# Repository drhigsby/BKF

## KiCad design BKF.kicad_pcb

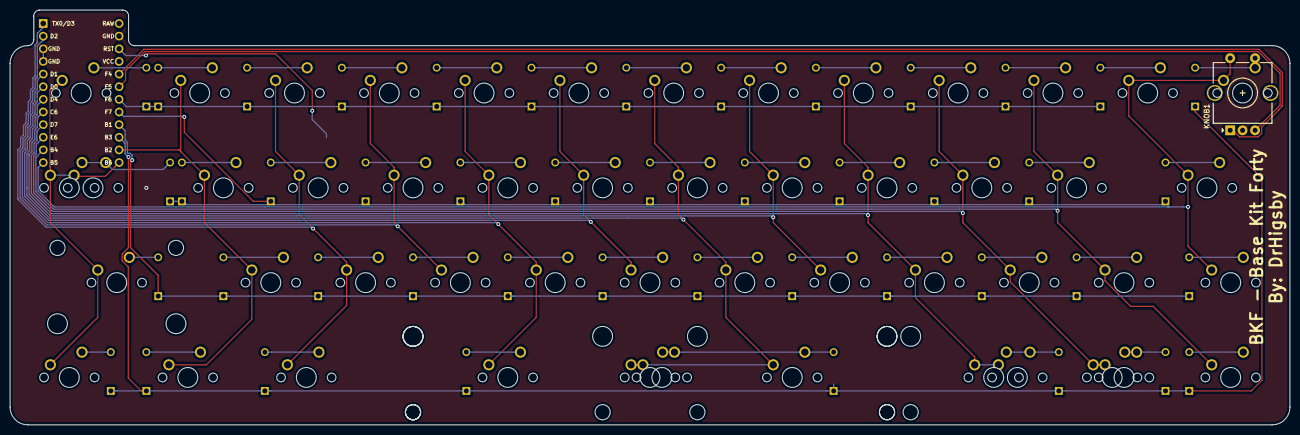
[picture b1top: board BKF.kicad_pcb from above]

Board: 2 copper layers, 257.2 x 83.3 mm, 98 parts (1 on the bottom side), 65 nets.

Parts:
D1, D2, D3, D4, D5, D6, D7, D8, D9, D10, D11, D12, D13, D14, D15, D16, D17, D18, D19, D20, D21, D22, D23, D24, D25, D26, D27, D28, D29, D30, D31, D32, D33, D34, D35, D36, D37, D38, D39, D40, D41, D42, D43, D44, D45: D_Small; Diode-Hybrid-Back
KNOB1: Rotary_Encoder_Switch; RotaryEncoder_Alps_EC11E-Switch_Vertical_H20mm_CircularMoun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
M13a1: MX-NoLED; MXOnly-1.25U-NoLED
MX1: MX-NoLED; MXOnly-1.5U-NoLED
MX2, MX3, MX4, MX5, MX6, MX7, MX8, MX9, MX10, MX11, MX12, MX14, MX15, MX16, MX17, MX18, MX19, MX20, MX21, MX22, MX23, MX26, MX27, MX28, MX29, MX30, MX31, MX32, MX33, MX34, MX35, MX43a1, MX45: MX-NoLED; MXOnly-1U-NoLED
MX13, MX24: MX-NoLED; MXOnly-1.75U-NoLED
MX25: MX-NoLED; MXOnly-2.25U-NoLED
MX36, MX37, MX38, MX39, MX42, MX42a1, MX43, MX44: MX-NoLED; MXOnly-1.25U-NoLED
MX40, MX41: MX-NoLED; MXOnly-3U-ReversedStabilizers-NoLED
MX41a1: MX-NoLED; MXOnly-6U-Centered-ReversedStabilizers-NoLED
MX41b1: MX-NoLED; MXOnly-6.25U-ReversedStabilizers-NoLED
PM1: ProMicro; ArduinoProMicro
RESET1: SW_Push; SKQG-1155865

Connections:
C1: M13a1.1, MX1.1, MX13.1, MX25.1, MX37.1, PM1.13
C2: MX2.1, MX14.1, MX26.1, MX38.1, PM1.14
C3: MX3.1, MX15.1, MX27.1, MX39.1, PM1.1
C4: MX4.1, MX16.1, MX28.1, PM1.2
C5: MX5.1, MX17.1, MX29.1, MX40.1, PM1.5
C6: MX6.1, MX18.1, MX30.1, PM1.6
C7: MX7.1, MX19.1, MX31.1, MX41.1, MX41a1.1, MX41b1.1, PM1.7
C8: MX8.1, MX20.1, MX32.1, PM1.8
C9: MX9.1, MX21.1, MX33.1, MX42.1, MX42a1.1, PM1.9
C10: MX10.1, MX22.1, MX34.1, MX43.1, MX43a1.1, PM1.10
C11: MX11.1, MX23.1, MX35.1, MX44.1, PM1.11
C12: KNOB1.S2, MX12.1, MX24.1, MX36.1, MX45.1, PM1.12
GND: KNOB1.C, PM1.3, PM1.4, PM1.23, RESET1.2
MTX1: D45.2, KNOB1.S1, MX45.2
unnamed: D1.2, MX1.2
unnamed: D2.2, MX2.2
unnamed: D3.2, MX3.2
unnamed: D4.2, MX4.2
unnamed: D5.2, MX5.2
unnamed: D6.2, MX6.2
unnamed: D7.2, MX7.2
unnamed: D8.2, MX8.2
unnamed: D9.2, MX9.2
unnamed: D10.2, MX10.2
unnamed: D11.2, MX11.2
unnamed: D12.2, MX12.2
unnamed: D13.2, M13a1.2, MX13.2
unnamed: D14.2, MX14.2
unnamed: D15.2, MX15.2
unnamed: D16.2, MX16.2
unnamed: D17.2, MX17.2
unnamed: D18.2, MX18.2
unnamed: D19.2, MX19.2
unnamed: D20.2, MX20.2
unnamed: D21.2, MX21.2
unnamed: D22.2, MX22.2
unnamed: D23.2, MX23.2
unnamed: D24.2, MX24.2
unnamed: D25.2, MX25.2
unnamed: D26.2, MX26.2
unnamed: D27.2, MX27.2
unnamed: D28.2, MX28.2
unnamed: D29.2, MX29.2
unnamed: D30.2, MX30.2
unnamed: D31.2, MX31.2
unnamed: D32.2, MX32.2
unnamed: D33.2, MX33.2
unnamed: D34.2, MX34.2
unnamed: D35.2, MX35.2
unnamed: D36.2, MX36.2
unnamed: D37.2, MX37.2
unnamed: D38.2, MX38.2
unnamed: D39.2, MX39.2
unnamed: D40.2, MX40.2
unnamed: D41.2, MX41.2, MX41a1.2, MX41b1.2
unnamed: D42.2, MX42.2, MX42a1.2
unnamed: D43.2, MX43.2, MX43a1.2
unnamed: D44.2, MX44.2
PM1: KNOB1.A, PM1.20
PM2: KNOB1.B, PM1.19
R1: D1.1, D2.1, D3.1, D4.1, D5.1, D6.1, D7.1, D8.1, D9.1, D10.1, D11.1, D12.1, PM1.18
R2: D13.1, D14.1, D15.1, D16.1, D17.1, D18.1, D19.1, D20.1, D21.1, D22.1, D23.1, D24.1, PM1.17
R3: D25.1, D26.1, D27.1, D28.1, D29.1, D30.1, D31.1, D32.1, D33.1, D34.1, D35.1, D36.1, PM1.16
R4: D37.1, D38.1, D39.1, D40.1, D41.1, D42.1, D43.1, D44.1, D45.1, PM1.15
RST: PM1.22, RESET1.1
